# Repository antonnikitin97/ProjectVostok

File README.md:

# Project Vostok
Hello and welcome to my project repo! Here you will find the schematic files and (eventually) firmware files pertaining to my project!

## What is Project Vostok?
A few months back, I bought myself a [TV-B-Gone](http://www.tvbgone.com/) (a gag device that allows you to turn off any TV). After 
having some fun playing around and trolling people with it I had an idea of extending the device to add more functionality. 

The device in its original form ejected the IR codes in a sequential mannar, there was no way of selecting the TV to be turned off beforehand.
This means that if your TV was at the bottom of the list, it could take up to a minute (!!!) for your TV to turn off. From a trolling efficiency 
perspective, this is clearly not ideal!

To that end, this project extends the TV-B-Gone in the following way:
  - Add headers to allow for a LCD screen to be mounted
  - Add a rotary encoder with a push button to allow the GUI to be navigatable
  - Use of a bigger microcontroller to allow for more IO Pins and extended functionality
  
The original design notes for the TV-B-Gone are avaliable [here](https://cdn-learn.adafruit.com/downloads/pdf/tv-b-gone-kit.pdf)

## Licensing
The licence for this project is [Creative Commons 2.5](https://creativecommons.org/licenses/by/2.5/)

## Acknowledgements
These are the people that have helped make this project a reality:
  - [Mitch Altman](http://www.tvbgone.com/about-us/) - the creator of TV-B-Gone! Obviously without him I wouldn't have had the basis
  for this project
  - [Kier Davis](http://kierdavis.com/) - a (great) friend at university who taught me numerous things about PCB design and embedded 
  programming and offered his time and effort into verifying that my design would work as intended!
  - [ninjafrostpn](https://github.com/ninjafrostpn) - another amazing Marine Biologist friend who supported and encouraged me to carry
  on even when things were slow!
  - [Professor Steve R. Gunn](http://users.ecs.soton.ac.uk/srg) - Academic at the University of Southampton who designed the LCD board that   I used in this project.
  - The lab technicians on Level 2 of the Zepler Building at the University of Southampton - these wonderful people helped immensely in 
  sourcing components and providing general help and guidance!

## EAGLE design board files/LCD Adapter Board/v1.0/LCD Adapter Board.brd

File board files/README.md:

# Project Vostok
Hello and welcome to my project repo! Here you will find the schematic files and firmware files (eventually) pertaining to my project!

## What is Project Vostok?
A few months back, I bought myself a [TV-B-Gone](http://www.tvbgone.com/) (a gag device that allows you to turn off any TV). After 
having some fun playing around and trolling people with it I had an idea of extending the device to add more functionality. 

The device in its original form ejected the IR codes in a sequential mannar, there was no way of selecting the TV to be turned off beforehand.
This means that if your TV was at the bottom of the list, it could take up to a minute (!!!) for your TV to turn off. From a trolling efficiency 
perspective, this is clearly not ideal!

To that end, this project extends the TV-B-Gone in the following way:
  - Add headers to allow for a LCD screen to be mounted
  - Add a rotary encoder with a push button to allow the GUI to be navigatable
  - Use of a bigger microcontroller to allow for more IO Pins and extended functionality
  
The original design notes for the TV-B-Gone are avaliable [here](https://cdn-learn.adafruit.com/downloads/pdf/tv-b-gone-kit.pdf)

## Licensing
The licence for this project is [Creative Commons 2.5](https://creativecommons.org/licenses/by/2.5/)

## Acknowledgements
These are the people that have helped make this project a reality:
  - [Mitch Altman](http://www.tvbgone.com/about-us/) - the creator of TV-B-Gone! Obviously without him I wouldn't have had the basis
  for this project
  - [Kier Davis](http://kierdavis.com/) - a (great) friend at university who taught me numerous things about PCB design and embedded 
  programming and offered his time and effort into verifying that my design would work as intended!
  - [ninjafrostpn](https://github.com/ninjafrostpn) - another amazing Marine Biologist friend who supported and encouraged me to carry
  on even when things were slow!
  - The lab technicians on Level 2 of the Zepler Building at the University of Southampton - these wonderful people helped immensely in 
  sourcing components and providing general help and guidance!

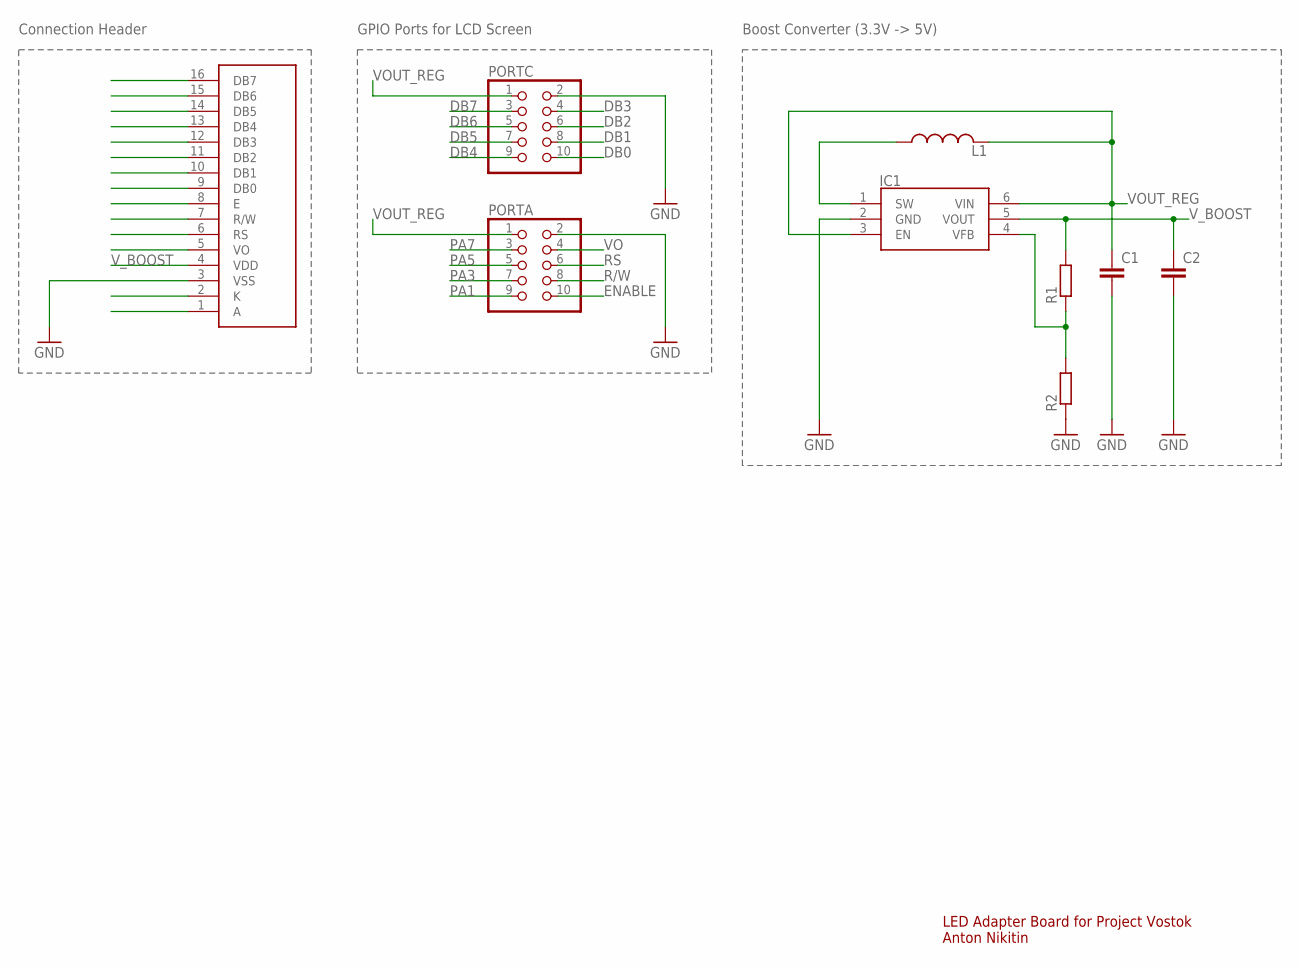
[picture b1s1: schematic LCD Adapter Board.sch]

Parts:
C1, C2: C-EUC0603; C0603
DS1: 162B-CC-BC-3LP; 162B
IC1: MCP1640BT-I_CHY; SOT95P270X145-6N
L1: L-USL0201; L0201
PORTA: PINHD-2X5; 2X05
PORTC: PINHD-2X5; 2X05
R1, R2: R-EU_R0603; R0603

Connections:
DB0: PORTC.10
DB1: PORTC.8
DB2: PORTC.6
DB3: PORTC.4
DB4: PORTC.9
DB5: PORTC.7
DB6: PORTC.5
DB7: PORTC.3
ENABLE: PORTA.10
GND: C1.2, C2.2, DS1.3 (VSS), IC1.2 (GND), PORTA.2, PORTC.2, R2.1
unnamed: IC1.1 (SW), L1.1
unnamed: IC1.4 (VFB), R1.1, R2.2
PA1: PORTA.9
PA3: PORTA.7
PA5: PORTA.5
PA7: PORTA.3
R/W: PORTA.8
RS: PORTA.6
VO: PORTA.4
VOUT_REG: C1.1, IC1.3 (EN), IC1.6 (VIN), L1.2, PORTA.1, PORTC.1
V_BOOST: C2.1, DS1.4 (VDD), IC1.5 (VOUT), R1.2

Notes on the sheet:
LED Adapter Board for Project Vostok Anton Nikitin
Connection Header
GPIO Ports for LCD Screen
Boost Converter (3.3V -> 5V)

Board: 2 copper layers, 9 parts (0 on the bottom side), 5 nets, no tracks yet.

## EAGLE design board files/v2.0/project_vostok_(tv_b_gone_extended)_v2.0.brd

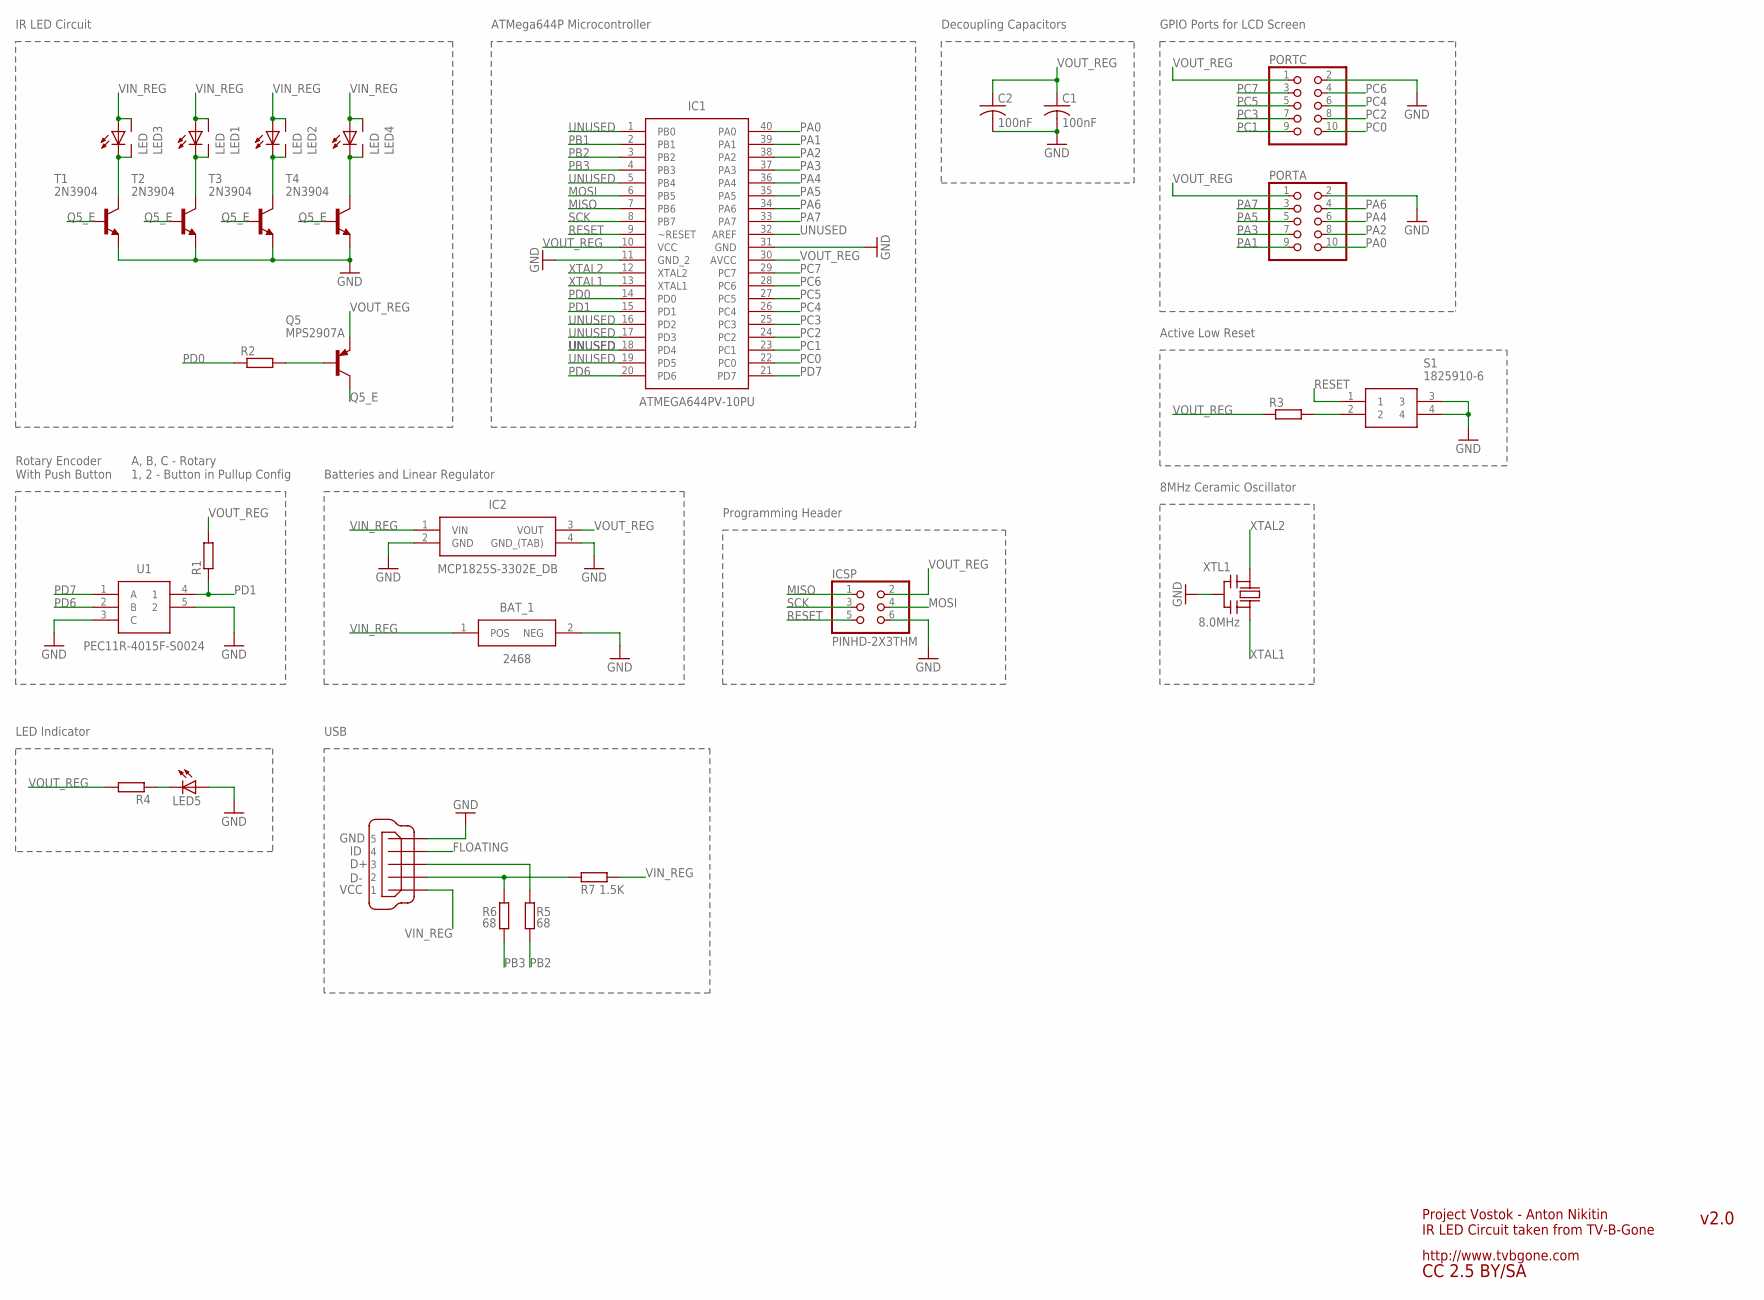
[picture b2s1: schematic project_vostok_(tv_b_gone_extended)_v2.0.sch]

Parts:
BAT_1: 2468
C1, C2: 100nF; C025-025X050
IC1: ATMEGA644PV-10PU; DIP254P1524X483-40
IC2: MCP1825S-3302E_DB; SOT230P700X180-4N
ICSP: PINHD-2X3THM; ISP6
LED1, LED2, LED3, LED4: LED; 5MM-SIDE
LED5: LED5MM
PORTA: PINHD-2X5; 2X05
PORTC: PINHD-2X5; 2X05
Q5: MPS2907A; TO92-CBE
R1, R2, R3, R4: R-EU_0204/7; 0204/7
R5, R6: 68; 0204/7
R7: 1.5K; 0204/7
S1: 1825910-6
T1, T2, T3, T4: 2N3904; TO92
U1: PEC11R-4015F-S0024; PEC12R-4XXXF-SXXXX_1
X1: MINI-USB_SHIELD5P2-32005-601; 32005-601
XTL1: 8.0MHz; CERM_OSC

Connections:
GND: BAT_1.2 (NEG), C1.2, C2.2, IC1.11 (GND_2), IC1.31 (GND), IC2.2 (GND), IC2.4 (GND_(TAB)), ICSP.6, LED5.A, PORTA.2, PORTC.2, S1.3, S1.4, T1.3 (E), T2.3 (E), T3.3 (E), T4.3 (E), U1.3 (C), U1.5 (2), X1.5, XTL1.P$2 (GND)
MISO: IC1.7 (PB6), ICSP.1
MOSI: IC1.6 (PB5), ICSP.4
unnamed: R5.1, X1.3
unnamed: LED5.K (C), R4.1
unnamed: R3.2, S1.2
unnamed: R6.1, R7.1, X1.2
unnamed: Q5.B, R2.2
PA0: IC1.40 (PA0), PORTA.10
PA1: IC1.39 (PA1), PORTA.9
PA2: IC1.38 (PA2), PORTA.8
PA3: IC1.37 (PA3), PORTA.7
PA4: IC1.36 (PA4), PORTA.6
PA5: IC1.35 (PA5), PORTA.5
PA6: IC1.34 (PA6), PORTA.4
PA7: IC1.33 (PA7), PORTA.3
PB2: IC1.3 (PB2), R5.2
PB3: IC1.4 (PB3), R6.2
PB4: IC1.5 (PB4)
PC0: IC1.22 (PC0), PORTC.10
PC1: IC1.23 (PC1), PORTC.9
PC2: IC1.24 (PC2), PORTC.8
PC3: IC1.25 (PC3), PORTC.7
PC4: IC1.26 (PC4), PORTC.6
PC5: IC1.27 (PC5), PORTC.5
PC6: IC1.28 (PC6), PORTC.4
PC7: IC1.29 (PC7), PORTC.3
PD0: IC1.14 (PD0), R2.1
PD1: IC1.15 (PD1), R1.1, U1.4 (1)
PD6: IC1.20 (PD6), U1.2 (B)
PD7: IC1.21 (PD7), U1.1 (A)
Q5_E: Q5.C, T1.2 (B), T2.2 (B), T3.2 (B), T4.2 (B)
RESET: IC1.9 (~RESET), ICSP.5, S1.1
SCK: IC1.8 (PB7), ICSP.3
T1_C: LED3.K (C), LED3.K2 (C1), T1.1 (C)
T2_C: LED1.K (C), LED1.K2 (C1), T2.1 (C)
T3_C: LED2.K (C), LED2.K2 (C1), T3.1 (C)
T4_C: LED4.K (C), LED4.K2 (C1), T4.1 (C)
UNUSED: IC1.2 (PB1)
VIN_REG: BAT_1.1 (POS), IC2.1 (VIN), LED1.A, LED1.A2 (A1), LED2.A, LED2.A2 (A1), LED3.A, LED3.A2 (A1), LED4.A, LED4.A2 (A1), R7.2, X1.1
VOUT_REG: C1.1, C2.1, IC1.10 (VCC), IC1.30 (AVCC), IC2.3 (VOUT), ICSP.2, PORTA.1, PORTC.1, Q5.E, R1.2, R3.1, R4.2
XTAL1: IC1.13 (XTAL1), XTL1.P$3 (OUT)
XTAL2: IC1.12 (XTAL2), XTL1.P$1 (IN)

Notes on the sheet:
XTAL1
XTAL2
MOSI
MISO
SCK
RESET
PA0
PA1
PA2
PA3
PA4
PA5
PA6
PA7
PC0
PC1
PC2
PC3
PC4
PC5
PC6
PC7
PB1
VOUT_REG
UNUSED
PB2
PB3
http://www.tvbgone.com
Project Vostok - Anton Nikitin IR LED Circuit taken from TV-B-Gone
v2.0
CC 2.5 BY/SA
IR LED Circuit
Rotary Encoder With Push Button
A, B, C - Rotary 1, 2 - Button in Pullup Config
Batteries and Linear Regulator
ATMega644P Microcontroller
Decoupling Capacitors
GPIO Ports for LCD Screen
Active Low Reset
8MHz Ceramic Oscillator

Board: 2 copper layers, 29 parts (0 on the bottom side), 41 nets, no tracks yet.

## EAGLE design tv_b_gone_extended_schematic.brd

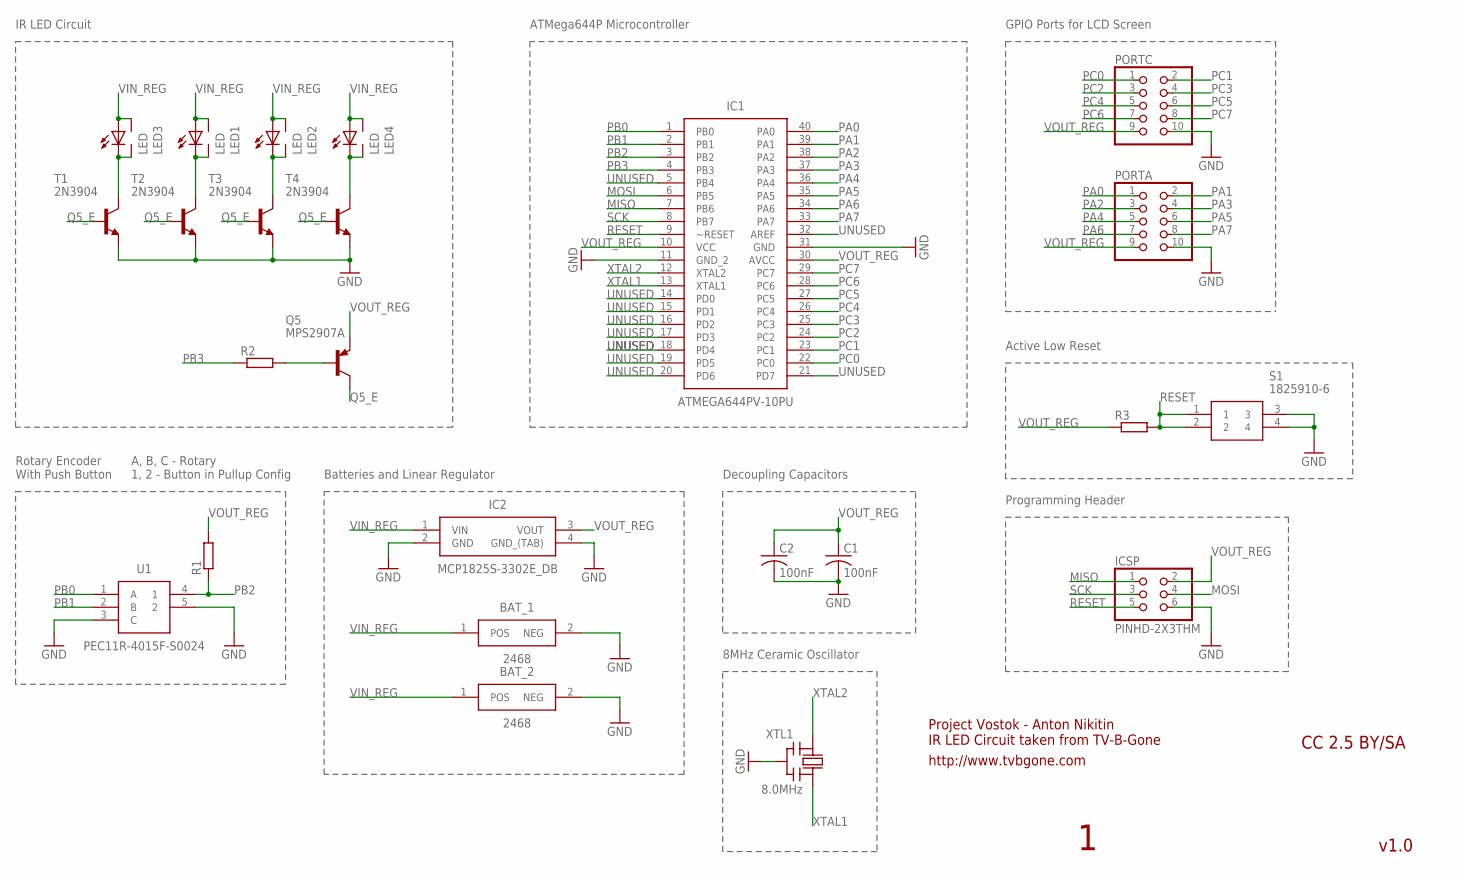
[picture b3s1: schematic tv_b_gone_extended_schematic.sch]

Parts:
BAT_1, BAT_2: 2468
C1, C2: 100nF; C025-025X050
IC1: ATMEGA644PV-10PU; DIP254P1524X483-40
IC2: MCP1825S-3302E_DB; SOT230P700X180-4N
ICSP: PINHD-2X3THM; ISP6
LED1, LED2, LED3, LED4: LED; 5MM-SIDE
PORTA: PINHD-2X5; 2X05
PORTC: PINHD-2X5; 2X05
Q5: MPS2907A; TO92-CBE
R1, R2: R-EU_0204/5; 0204/5
R3: R-EU_0204/7; 0204/7
S1: 1825910-6
T1, T2, T3, T4: 2N3904; TO92
U1: PEC11R-4015F-S0024; PEC12R-4XXXF-SXXXX_1
XTL1: 8.0MHz; CERM_OSC

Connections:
GND: BAT_1.2 (NEG), BAT_2.2 (NEG), C1.2, C2.2, IC1.11 (GND_2), IC1.31 (GND), IC2.2 (GND), IC2.4 (GND_(TAB)), ICSP.6, PORTA.10, PORTC.10, S1.3, S1.4, T1.3 (E), T2.3 (E), T3.3 (E), T4.3 (E), U1.3 (C), U1.5 (2), XTL1.P$2 (GND)
MISO: IC1.7 (PB6), ICSP.1
MOSI: IC1.6 (PB5), ICSP.4
unnamed: Q5.B, R2.2
PA0: IC1.40 (PA0), PORTA.1
PA1: IC1.39 (PA1), PORTA.2
PA2: IC1.38 (PA2), PORTA.3
PA3: IC1.37 (PA3), PORTA.4
PA4: IC1.36 (PA4), PORTA.5
PA5: IC1.35 (PA5), PORTA.6
PA6: IC1.34 (PA6), PORTA.7
PA7: IC1.33 (PA7), PORTA.8
PB0: IC1.1 (PB0), U1.1 (A)
PB1: IC1.2 (PB1), U1.2 (B)
PB2: IC1.3 (PB2), R1.1, U1.4 (1)
PB3: IC1.4 (PB3), R2.1
PC0: IC1.22 (PC0), PORTC.1
PC1: IC1.23 (PC1), PORTC.2
PC2: IC1.24 (PC2), PORTC.3
PC3: IC1.25 (PC3), PORTC.4
PC4: IC1.26 (PC4), PORTC.5
PC5: IC1.27 (PC5), PORTC.6
PC6: IC1.28 (PC6), PORTC.7
PC7: IC1.29 (PC7), PORTC.8
Q5_E: Q5.C, T1.2 (B), T2.2 (B), T3.2 (B), T4.2 (B)
RESET: IC1.9 (~RESET), ICSP.5, R3.2, S1.1, S1.2
SCK: IC1.8 (PB7), ICSP.3
T1_C: LED3.K (C), LED3.K2 (C1), T1.1 (C)
T2_C: LED1.K (C), LED1.K2 (C1), T2.1 (C)
T3_C: LED2.K (C), LED2.K2 (C1), T3.1 (C)
T4_C: LED4.K (C), LED4.K2 (C1), T4.1 (C)
VIN_REG: BAT_1.1 (POS), BAT_2.1 (POS), IC2.1 (VIN), LED1.A, LED1.A2 (A1), LED2.A, LED2.A2 (A1), LED3.A, LED3.A2 (A1), LED4.A, LED4.A2 (A1)
VOUT_REG: C1.1, C2.1, IC1.10 (VCC), IC1.30 (AVCC), IC2.3 (VOUT), ICSP.2, PORTA.9, PORTC.9, Q5.E, R1.2, R3.1
XTAL1: IC1.13 (XTAL1), XTL1.P$3 (OUT)
XTAL2: IC1.12 (XTAL2), XTL1.P$1 (IN)

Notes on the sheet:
XTAL1
XTAL2
MOSI
MISO
SCK
RESET
PA0
PA1
PA2
PA3
PA4
PA5
PA6
PA7
PC0
PC1
PC2
PC3
PC4
PC5
PC6
PC7
PB0
PB1
VOUT_REG
UNUSED
PB2
PB3
http://www.tvbgone.com
Project Vostok - Anton Nikitin IR LED Circuit taken from TV-B-Gone
v1.0
CC 2.5 BY/SA
IR LED Circuit
Rotary Encoder With Push Button
A, B, C - Rotary 1, 2 - Button in Pullup Config
Batteries and Linear Regulator
ATMega644P Microcontroller
Decoupling Capacitors
GPIO Ports for LCD Screen
Active Low Reset

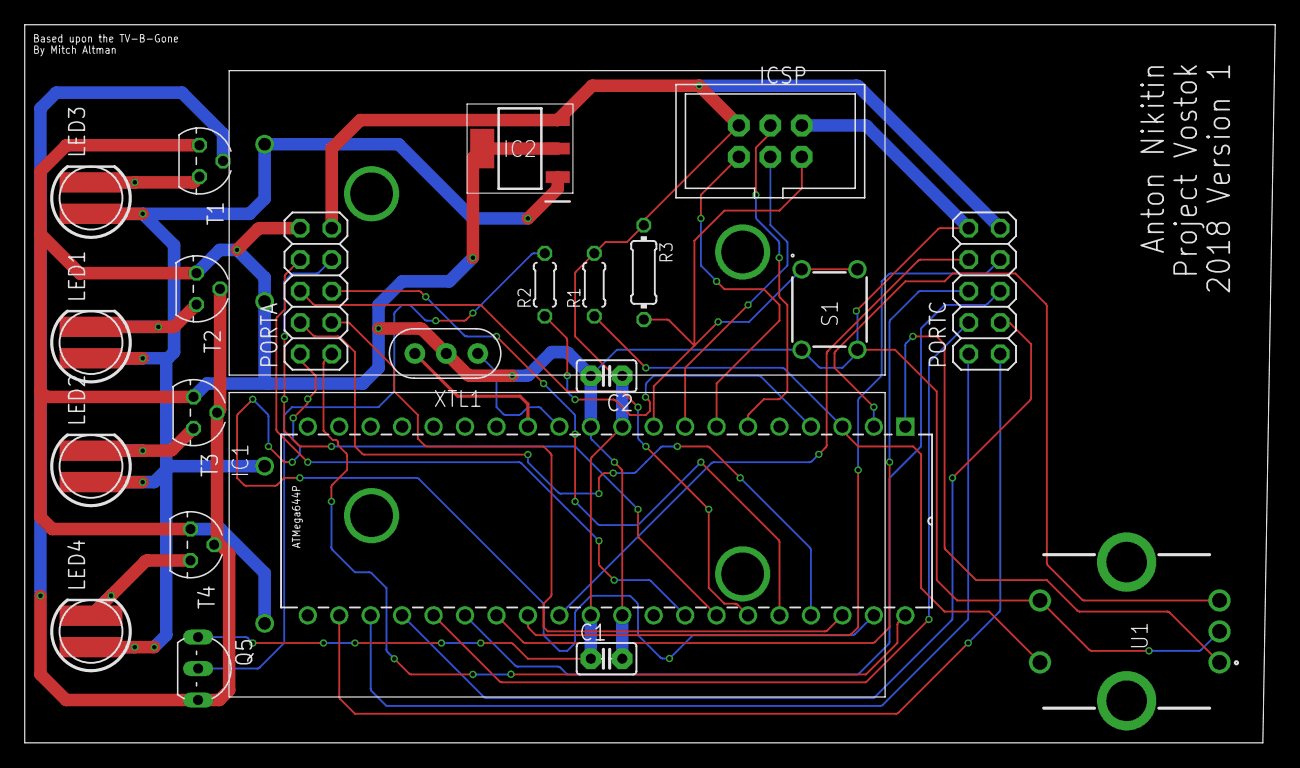
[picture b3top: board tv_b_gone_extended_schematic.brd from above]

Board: 2 copper layers, 101.0 x 58.0 mm, 24 parts (0 on the bottom side), 35 nets.

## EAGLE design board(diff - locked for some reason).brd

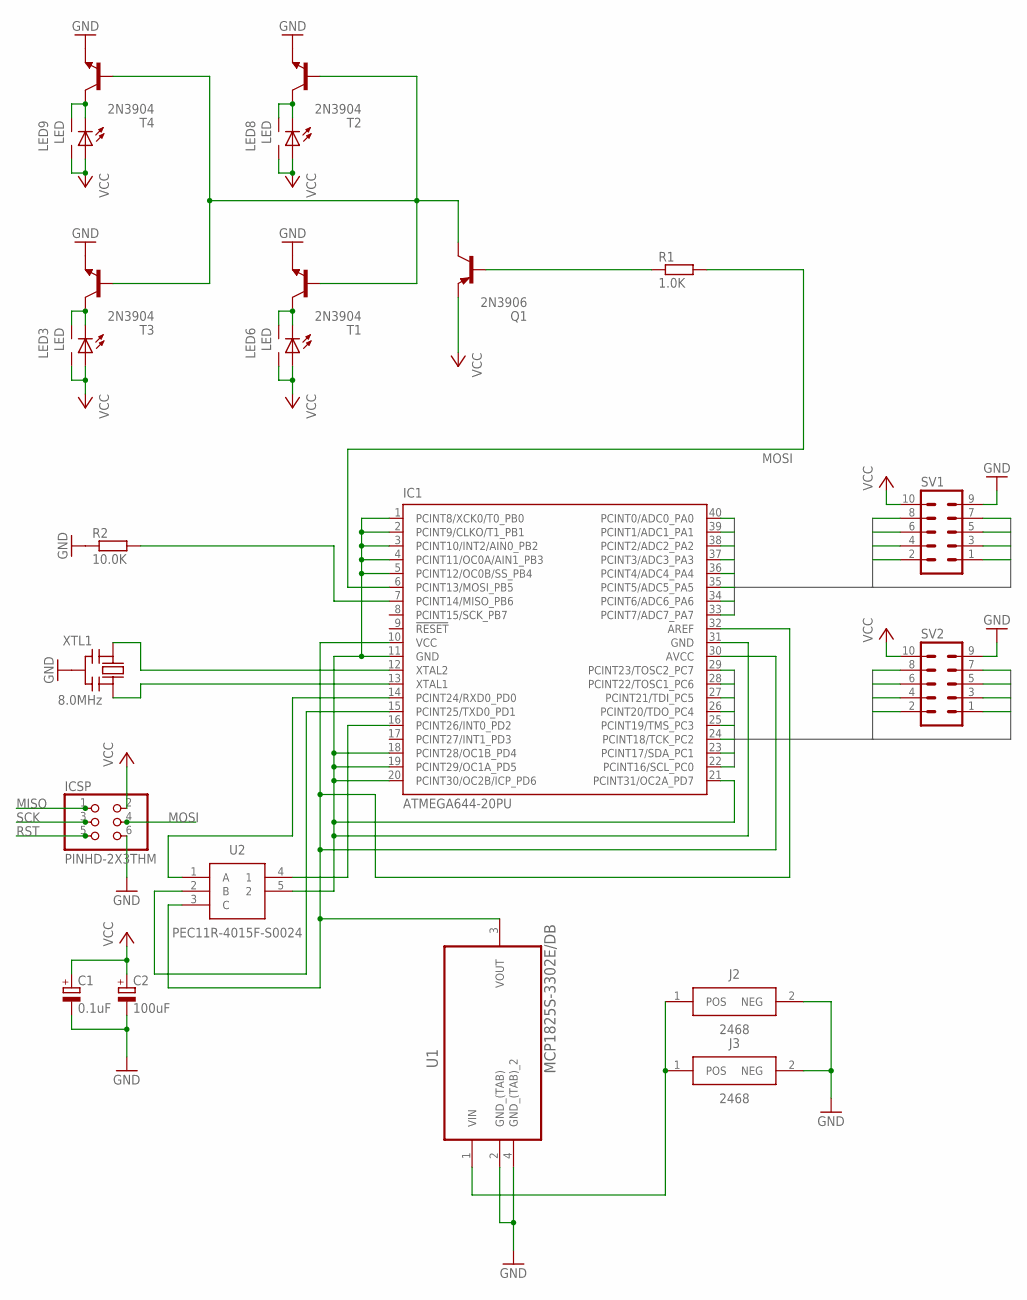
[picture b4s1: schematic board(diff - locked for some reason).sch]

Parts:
C1: 0.1uF; E2,5-6E
C2: 100uF; E2,5-6E
IC1: ATMEGA644-20PU; DIL40
ICSP: PINHD-2X3THM; ISP6
J2, J3: 2468
LED3, LED6, LED8, LED9: LED; 5MM-SIDE
Q1: 2N3906; TO92
R1: 1.0K; 0207/7
R2: 10.0K; 0207/7
SV1, SV2: MA05-2
T1, T2, T3, T4: 2N3904; TO92
U1: MCP1825S-3302E/DB; SOT230P700X180-4N
U2: PEC11R-4015F-S0024; PEC12R-4XXXF-SXXXX_1
XTL1: 8.0MHz; CERM_OSC

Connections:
GND: C1.-, C2.-, ICSP.6, J2.2 (NEG), J3.2 (NEG), R2.1, SV1.9, SV2.9, T1.3 (E), T2.3 (E), T3.3 (E), T4.3 (E), U1.2 (GND_(TAB)), U1.4 (GND_(TAB)_2), XTL1.P$2 (GND)
MISO: ICSP.1
MOSI: IC1.6 (PCINT13/MOSI_PB5), ICSP.4, R1.2
unnamed: LED6.K (C), LED6.K2 (C1), T1.1 (C)
unnamed: LED3.K (C), LED3.K2 (C1), T3.1 (C)
unnamed: LED8.K (C), LED8.K2 (C1), T2.1 (C)
unnamed: LED9.K (C), LED9.K2 (C1), T4.1 (C)
unnamed: Q1.1 (C), T1.2 (B), T2.2 (B), T3.2 (B), T4.2 (B)
unnamed: IC1.14 (PCINT24/RXD0_PD0), U2.1 (A)
unnamed: IC1.15 (PCINT25/TXD0_PD1), U2.2 (B)
unnamed: IC1.10 (VCC), IC1.30 (AVCC), IC1.32 (AREF), U1.3 (VOUT), U2.3 (C)
unnamed: IC1.12 (XTAL2), XTL1.P$1 (IN)
unnamed: IC1.13 (XTAL1), XTL1.P$3 (OUT)
unnamed: IC1.7 (PCINT14/MISO_PB6), R2.2
unnamed: IC1.16 (PCINT26/INT0_PD2), U2.4 (1)
unnamed: J2.1 (POS), J3.1 (POS), U1.1 (VIN)
unnamed: IC1.1 (PCINT8/XCK0/T0_PB0), IC1.2 (PCINT9/CLKO/T1_PB1), IC1.3 (PCINT10/INT2/AIN0_PB2), IC1.4 (PCINT11/OC0A/AIN1_PB3), IC1.5 (PCINT12/OC0B/SS_PB4), IC1.11 (GND), IC1.18 (PCINT28/OC1B_PD4), IC1.19 (PCINT29/OC1A_PD5), IC1.20 (PCINT30/OC2B/ICP_PD6), IC1.21 (PCINT31/OC2A_PD7), IC1.31 (GND), U2.5 (2)
unnamed: Q1.2 (B), R1.1
PA0: IC1.40 (PCINT0/ADC0_PA0), SV1.8
PA1: IC1.39 (PCINT1/ADC1_PA1), SV1.6
PA2: IC1.38 (PCINT2/ADC2_PA2), SV1.4
PA3: IC1.37 (PCINT3/ADC3_PA3), SV1.2
PA4: IC1.36 (PCINT4/ADC4_PA4), SV1.1
PA5: IC1.35 (PCINT5/ADC5_PA5), SV1.3
PA6: IC1.34 (PCINT6/ADC6_PA6), SV1.5
PA7: IC1.33 (PCINT7/ADC7_PA7), SV1.7
PC0: IC1.22 (PCINT16/SCL_PC0), SV2.8
PC1: IC1.23 (PCINT17/SDA_PC1), SV2.6
PC2: IC1.24 (PCINT18/TCK_PC2), SV2.4
PC3: IC1.25 (PCINT19/TMS_PC3), SV2.2
PC4: IC1.26 (PCINT20/TDO_PC4), SV2.1
PC5: IC1.27 (PCINT21/TDI_PC5), SV2.3
PC6: IC1.28 (PCINT22/TOSC1_PC6), SV2.5
PC7: IC1.29 (PCINT23/TOSC2_PC7), SV2.7
RST: ICSP.5
SCK: ICSP.3
VCC: C1.+, C2.+, ICSP.2, LED3.A, LED3.A2 (A1), LED6.A, LED6.A2 (A1), LED8.A, LED8.A2 (A1), LED9.A, LED9.A2 (A1), Q1.3 (E), SV1.10, SV2.10

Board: 2 copper layers, 22 parts (2 on the bottom side), 34 nets, no tracks yet.

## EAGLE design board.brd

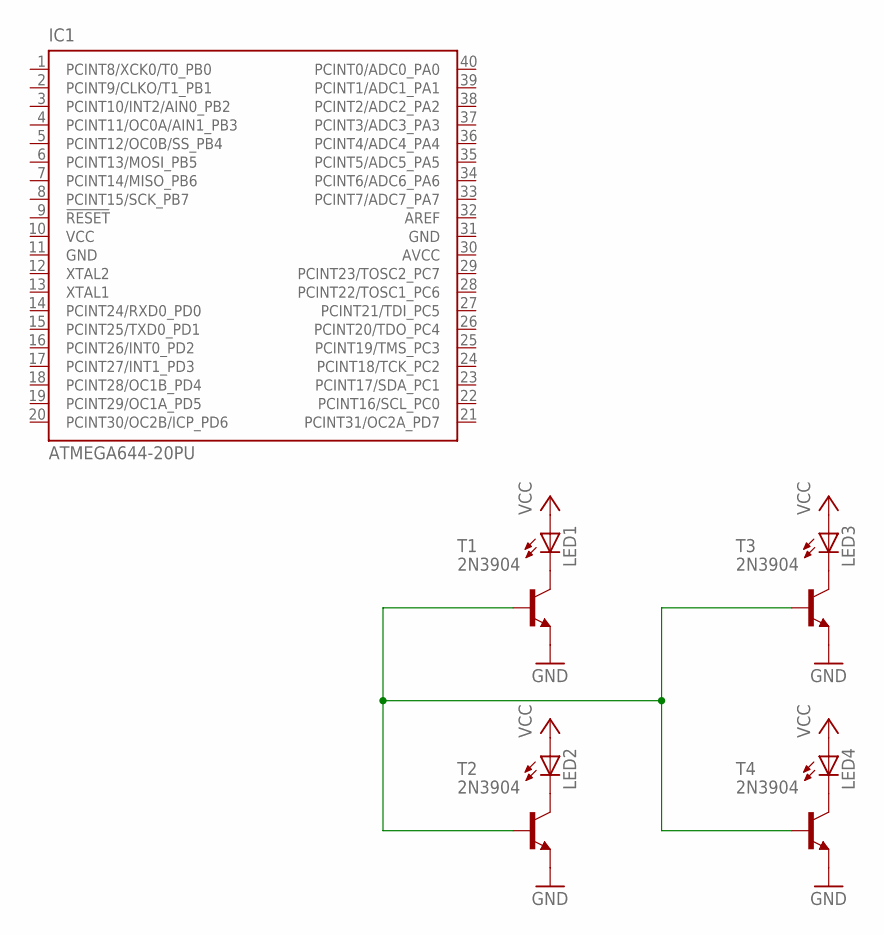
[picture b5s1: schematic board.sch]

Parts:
IC1: ATMEGA644-20PU; DIL40
LED1, LED2, LED3, LED4: LED3MM
T1, T2, T3, T4: 2N3904; TO92

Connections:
AVCC: IC1.30 (AVCC)
GND: IC1.11 (GND), IC1.31 (GND), T1.3 (E), T2.3 (E), T3.3 (E), T4.3 (E)
unnamed: LED1.K (C), T1.1 (C)
unnamed: LED3.K (C), T3.1 (C)
unnamed: LED2.K (C), T2.1 (C)
unnamed: LED4.K (C), T4.1 (C)
unnamed: T1.2 (B), T2.2 (B), T3.2 (B), T4.2 (B)
VCC: IC1.10 (VCC), LED1.A, LED2.A, LED3.A, LED4.A

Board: 2 copper layers, 9 parts (0 on the bottom side), 7 nets, no tracks yet.

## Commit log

2017-10-14 modified board and schematic for extra parts required - added decoupling capacitors
2017-10-24 modified design and added ada library
2017-11-01 modified board some more
2017-11-02 modified board slightly
2017-11-02 added battery holders
2017-11-02 modified board to remove extra battery
2017-11-02 modified board layout
2017-11-03 modified board
2017-11-06 modified board size
2017-11-16 finished connections on schematic
2018-02-03 removed all my old crap
2018-02-03 added new files
2018-02-05 made progress
2018-02-14 made progress - Thanks Kier :)
2018-02-15 routing
2018-02-15 organise schematic and make changes to board
2018-02-15 remove garbage files and add detail to schem
2018-02-15 change name
2018-02-15 add .gitignore
2018-02-15 removed .epf
2018-02-15 changed file structure
2018-02-15 move readme
2018-02-15 add reference
2018-02-17 removed wires and change battery orientation
2018-02-25 modified routing
2018-03-11 move to v1.0 folder - create 1.1
2018-03-14 add version 1.1 of schematic
2018-03-14 add acknowledgement
2018-03-14 modify port
2018-04-08 add usb
2018-08-30 add voltage pin to USB
2018-08-30 move components on board
2018-08-30 rename version 1.0 file
2018-08-30 add v1.1 pdf schematic
2018-08-30 modify component placements
2018-08-31 move components and begin wiring
2018-08-31 make progress on wiring
2018-09-08 ripup traces for movement of components
2018-10-09 modify component positions on board
2018-10-10 tidy labels on board
2018-10-10 remove old gitignore
2018-10-10 add new gitignore
2018-10-10 modify labels for board
2018-10-11 begin wiring
2018-10-11 modify pin assignments for rotary encoder
2018-10-11 make further progress on wiring
2018-10-11 export new schematic to reflect pin changes
2018-10-11 work on wiring
2019-11-17 update schematic and update pdf
2020-03-09 move files into main board folder
2020-03-09 add version 2.0 files
2020-03-09 re-organise file structure for main board/adapter board
2020-03-09 re-organise reference folder structure
2020-03-11 add LCD adapter board eagle files
2020-03-13 add boost converter
